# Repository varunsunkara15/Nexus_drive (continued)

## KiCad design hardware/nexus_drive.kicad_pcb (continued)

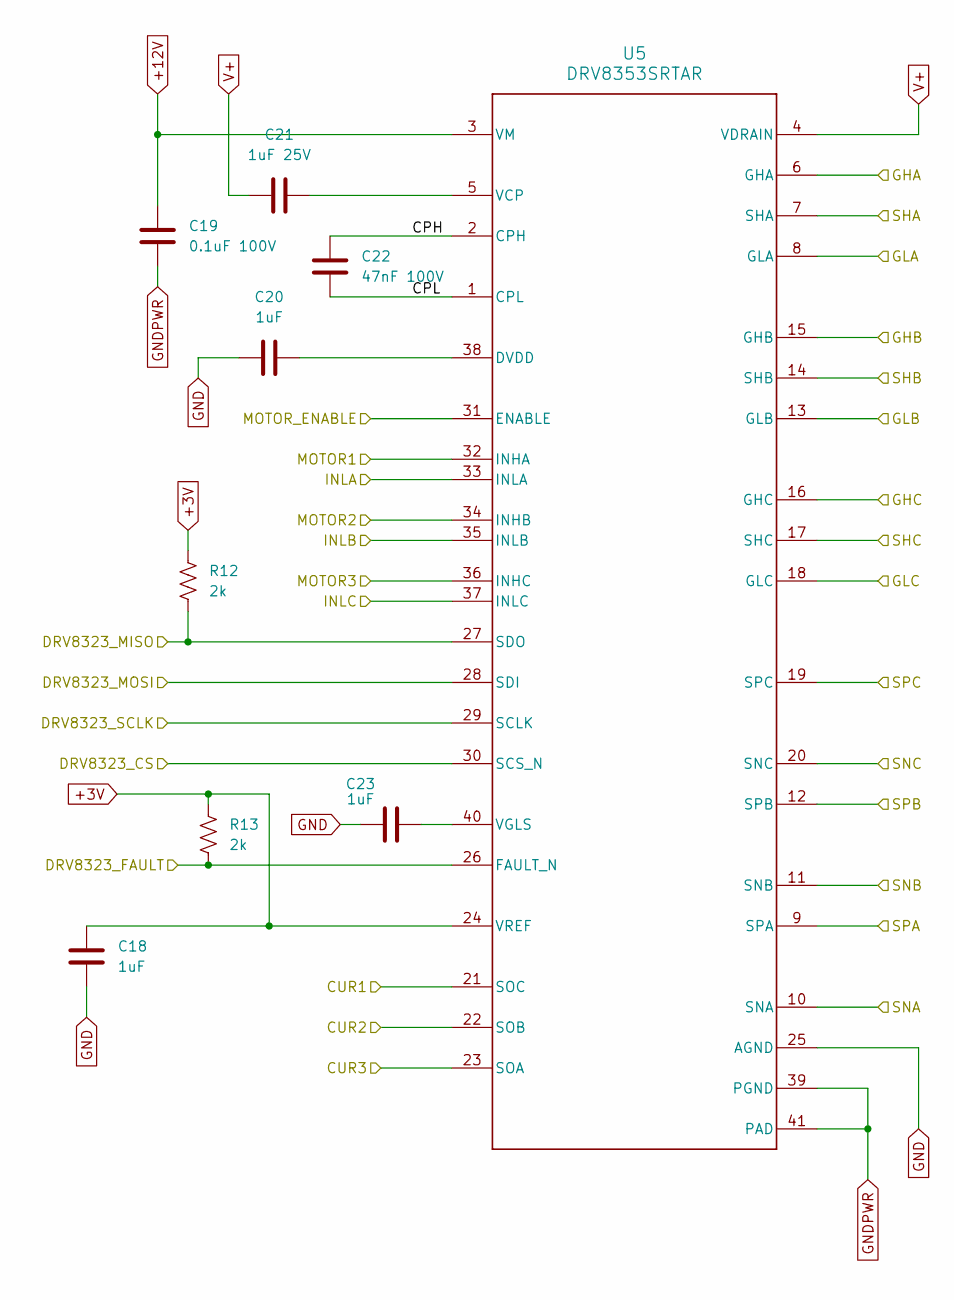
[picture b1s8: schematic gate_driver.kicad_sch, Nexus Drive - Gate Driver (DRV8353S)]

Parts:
C18: 1uF; C_0603_1608Metric; MPN MF-CAP-0603-1uF
C19: 0.1uF 100V; C_0603_1608Metric; MPN GCJ188R72A104KA01D
C20: 1uF; C_0402_1005Metric; MPN MF-CAP-0402-1uF
C21: 1uF 25V; C_0603_1608Metric; MPN C1608X7R1E105K080AE
C22: 47nF 100V; C_0603_1608Metric; MPN C0603X473K1RAC7867
C23: 1uF; C_0603_1608Metric; MPN C1608X7R1E105K080AE
R12, R13: 2k; R_0402_1005Metric; MPN MF-RES-0402-2K
U5: DRV8353SRTAR; RTA0040B; MPN DRV8353SRTAR

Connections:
+3V: C18.2, R12.1, R13.1, U5.24 (VREF); also elsewhere on the board
+12V: C19.2, U5.3 (VM)
/CUR1: U5.21 (SOC); also elsewhere on the board
/CUR2: U5.22 (SOB); also elsewhere on the board
/CUR3: U5.23 (SOA); also elsewhere on the board
/DRV_SCLK: U5.29 (SCLK); also elsewhere on the board
/DRV_SDI: U5.28 (SDI); also elsewhere on the board
/DRV_SDO: R12.2, U5.27 (SDO); also elsewhere on the board
/DRV_nCS: U5.30 (SCS_N); also elsewhere on the board
/DRV_nFAULT: R13.2, U5.26 (FAULT_N); also elsewhere on the board
/GATE_EN: U5.31 (ENABLE); also elsewhere on the board
/GHA: U5.6 (GHA); also elsewhere on the board
/GHB: U5.15 (GHB); also elsewhere on the board
/GHC: U5.16 (GHC); also elsewhere on the board
/GLA: U5.8 (GLA); also elsewhere on the board
/GLB: U5.13 (GLB); also elsewhere on the board
/GLC: U5.18 (GLC); also elsewhere on the board
/Gate Driver/CPH: C22.2, U5.2 (CPH)
/Gate Driver/CPL: C22.1, U5.1 (CPL)
/PWM_AH: U5.32 (INHA); also elsewhere on the board
/PWM_AL: U5.33 (INLA); also elsewhere on the board
/PWM_BH: U5.34 (INHB); also elsewhere on the board
/PWM_BL: U5.35 (INLB); also elsewhere on the board
/PWM_CH: U5.36 (INHC); also elsewhere on the board
/PWM_CL: U5.37 (INLC); also elsewhere on the board
/SHA: U5.7 (SHA); also elsewhere on the board
/SHB: U5.14 (SHB); also elsewhere on the board
/SHC: U5.17 (SHC); also elsewhere on the board
/SNA: U5.10 (SNA); also elsewhere on the board
/SNB: U5.11 (SNB); also elsewhere on the board
/SNC: U5.20 (SNC); also elsewhere on the board
/SPA: U5.9 (SPA); also elsewhere on the board
/SPB: U5.12 (SPB); also elsewhere on the board
/SPC: U5.19 (SPC); also elsewhere on the board
GND: C18.1, C20.1, C23.1, U5.25 (AGND); also elsewhere on the board
GNDPWR: C19.1, U5.39 (PGND), U5.41 (PAD); also elsewhere on the board
unnamed: C20.2, U5.38 (DVDD)
unnamed: C21.2, U5.5 (VCP)
unnamed: C23.2, U5.40 (VGLS)
V+: C21.1, U5.4 (VDRAIN); also elsewhere on the board

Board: 2 copper layers, 116 parts (0 on the bottom side), 103 nets, no tracks yet.

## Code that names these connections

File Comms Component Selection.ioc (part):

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board=custom
Mcu.Name=STM32G474M(B-C-E)Tx
Mcu.Package=LQFP80
Mcu.UserName=STM32G474METx
PA0.GPIO_Label=CURR_A
PA0.GPIOParameters=GPIO_Label
PA0.Mode=IN1-Single-Ended
PA0.Signal=ADC1_IN1
PA10.Signal=S_TIM1_CH3
PA11.Mode=FDCAN_Activate
PA11.Signal=FDCAN1_RX
PA12.Mode=FDCAN_Activate
PA12.Signal=FDCAN1_TX
PA13.Mode=Serial_Wire
PA13.Signal=SYS_JTMS-SWDIO
PA14.Mode=Serial_Wire
PA14.Signal=SYS_JTCK-SWCLK
PA6.Mode=Full_Duplex_Master
PA6.Signal=SPI1_MISO
PA7.Mode=PWM Generation1 CH1 CH1N
PA7.Signal=TIM1_CH1N
PA8.Signal=S_TIM1_CH1
PA9.Signal=S_TIM1_CH2
PB1.Mode=PWM Generation3 CH3 CH3N
PB1.Signal=TIM1_CH3N
PB12.Mode=Activate-Break-Input
PB12.Signal=TIM1_BKIN
PB13.Mode=Full_Duplex_Master
PB13.Signal=SPI2_SCK
PB14.Mode=Full_Duplex_Master
PB14.Signal=SPI2_MISO
PB15.Mode=Full_Duplex_Master
PB15.Signal=SPI2_MOSI
PB3.Mode=Full_Duplex_Master
PB3.Signal=SPI1_SCK
PB5.Mode=Full_Duplex_Master
PB5.Signal=SPI1_MOSI
PC0.GPIO_Label=VPH_A
PC0.GPIOParameters=GPIO_Label
PC0.Mode=IN6-Single-Ended
PC0.Signal=ADC1_IN6
PC1.GPIO_Label=VPH_B
PC1.GPIOParameters=GPIO_Label
PC1.Mode=IN7-Single-Ended
PC1.Signal=ADC2_IN7
PC10.Mode=Full_Duplex_Master
PC10.Signal=SPI3_SCK
PC11.Mode=Full_Duplex_Master
PC11.Signal=SPI3_MISO
PC12.Mode=Full_Duplex_Master
PC12.Signal=SPI3_MOSI
PC3.GPIO_Label=CURR_B
PC3.GPIOParameters=GPIO_Label
PC3.Mode=IN9-Single-Ended
PC3.Signal=ADC2_IN9
PC4.GPIO_Label=GATE_EN
PC4.GPIOParameters=GPIO_Label
PC4.Signal=GPIO_Output
PC6.GPIO_Label=ENC1_CS
PC6.GPIOParameters=GPIO_Label
PC6.Signal=GPIO_Output
PC7.GPIO_Label=ENC2_CS
PC7.GPIOParameters=GPIO_Label
PC7.Signal=GPIO_Output
PC8.GPIO_Label=ENC3_CS
PC8.GPIOParameters=GPIO_Label
PC8.Signal=GPIO_Output
PC9.GPIO_Label=CAN_STB
PC9.GPIOParameters=GPIO_Label
PC9.Signal=GPIO_Output
PD10.Signal=GPIO_Output
PD8.GPIO_Label=TEMP_FET_LS
PD8.GPIOParameters=GPIO_Label
PD8.Mode=IN12-Single-Ended
PD8.Signal=ADC4_IN12
PE10.Mode=PWM Generation2 CH2 CH2N
PE10.Signal=TIM1_CH2N
PE11.GPIO_Label=TEMP_MOTOR
PE11.GPIOParameters=GPIO_Label
PE11.Mode=IN15-Single-Ended
PE11.Signal=ADC4_IN15
PE12.Mode=Full_Duplex_Master
PE12.Signal=SPI4_SCK
PE13.Mode=Full_Duplex_Master
PE13.Signal=SPI4_MISO
PE14.Mode=Full_Duplex_Master
PE14.Signal=SPI4_MOSI
PE15.GPIO_Label=VBUS
PE15.GPIOParameters=GPIO_Label
PE15.Mode=IN2-Single-Ended
PE15.Signal=ADC4_IN2
PE7.GPIO_Label=VPH_C
PE7.GPIOParameters=GPIO_Label
PE7.Mode=IN4-Single-Ended
PE7.Signal=ADC3_IN4
PE8.GPIO_Label=TEMP_FET_HS
PE8.GPIOParameters=GPIO_Label
PE8.Mode=IN6-Single-Ended
PE8.Signal=ADC4_IN6
PE9.GPIO_Label=CURR_C
PE9.GPIOParameters=GPIO_Label
PE9.Mode=IN2-Single-Ended
PE9.Signal=ADC3_IN2
PF0-OSC_IN.Mode=HSE-External-Oscillator
PF0-OSC_IN.Signal=RCC_OSC_IN
PF1-OSC_OUT.Mode=HSE-External-Oscillator
PF1-OSC_OUT.Signal=RCC_OSC_OUT
RCC.HSE_VALUE=16000000
RCC.SYSCLKFreq_VALUE=160000000
RCC.SYSCLKSource=RCC_SYSCLKSOURCE_PLLCLK
